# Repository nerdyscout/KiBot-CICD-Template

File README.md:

---

# KiCAD-CICD-Template

This repository provides different CI/CD workflows used for projects using [KiCAD](https://www.kicad.org/) and [PlatformIO](https://platformio.org).

## workflows

### KiBot

[KiBot](https://github.com/INTI-CMNB/KiBot/) is used to generate all kind of documentation from a KiCAD6 project.

Whenever a file matching `pcb/*.kicad_*` changes this workflow will trigger.

The following documents are generated on every build:

```
- pcb/cad/
   - dxf/
      - AutoCAD - DXF
   - boardview - BRD
   - 3D render - STEP
- pcb/docs/
   - bom/
      - Interactive BOM - HTML
      - Octopart list - CSV
      - KiCost - XLSX (disabled)
   - schematic - PDF
- pcb/img/
   - pcb/$fab/$style/
      - PCB top - SVG
      - PCB bottom - SVG
   - render/ (disabled)
      - PCB render - PNG
   - schematic - SVG
- pcb/gerbers - ZIP
```

### PlatformIO

used to rebuild your source code whenever it changes.

### REUSE

used to insure every file got a propper license. 

## getting started

- [ ] hit the "use this template" button and give your project a name
- [ ] clone this new repository localy
- [ ] replace content of README.md
- [ ] Code
   - [ ] put your code in the `src/` folder using platformio
- [ ] PCB
   - [ ] change the filenames in `pcb/*.kicad_*` matching your repository name
   - [ ] create your PCB
- [ ] run `reuse --lint`
   - [ ] make sure the licenses of `pcb/*` fits your needs
   - [ ] make sure the licenses of `src/*`, `include/*`, `lib/*`, `test/*` fits your needs
- [ ] commit and push all those changes regulary to your project

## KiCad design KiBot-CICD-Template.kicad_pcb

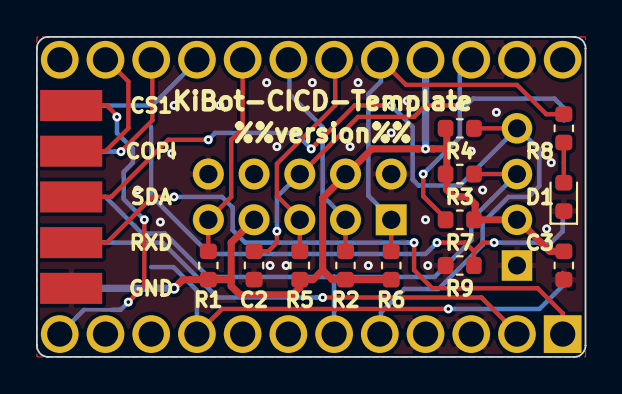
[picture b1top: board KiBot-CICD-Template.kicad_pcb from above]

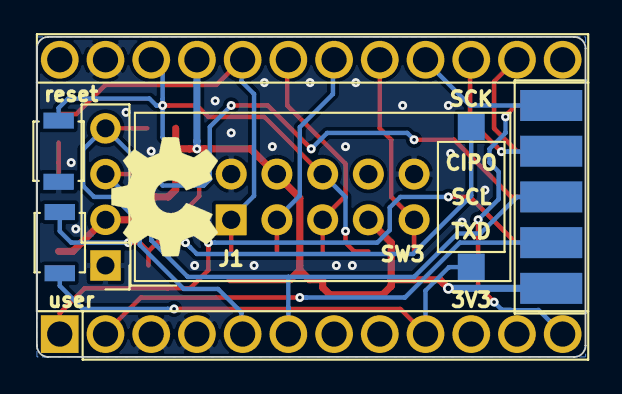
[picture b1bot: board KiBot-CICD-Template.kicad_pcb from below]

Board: 4 copper layers, 30.5 x 17.8 mm, 20 parts (8 on the bottom side), 18 nets.

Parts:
A1: Sparkfun_Pro_Micro
C2: 1µ; C_0603_1608Metric
C3: 100n; C_0603_1608Metric
D1: LED; LED_0603_1608Metric
J1: AVR-JTAG-10; IDC-Header_2x05_P2.54mm_Vertical
J2: UEXT_Host; UEXT
J3: Display; PinHeader_1x04_P2.54mm_Vertical
LOGO1: Logo_Open_Hardware_Small; OSHW-Symbol_6.7x6mm_SilkScreen
R1, R2, R3, R4, R5, R6, R7, R9: 4k7; R_0603_1608Metric
R8: 1k; R_0603_1608Metric
SW1: reset; SW_SPST_B3U-1000P
SW2: user; SW_SPST_B3U-1000P
SW3: user; SW_SPST_CK_RS282G05A3

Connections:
+3V3: A1.21, C3.1, J1.4, J1.7, J2.1, J3.2, R1.2, R2.2, R3.2, R4.2, R5.2, R6.2, R7.2
BTN: A1.9, SW2.2, SW3.2
CIPO: A1.15, J2.7
COPI: A1.14, J2.8
CS1: A1.12, J2.10
GND: A1.3, A1.4, A1.23, C2.2, C3.2, D1.1, J1.2, J1.10, J2.2, J3.1, R9.1, SW1.1
unnamed: D1.2, R8.1
unnamed: R9.2, SW2.1, SW3.1
RXD: A1.1, J2.4
SCK: A1.16, J2.9
SCL: A1.6, J2.5, J3.3, R3.1
SDA: A1.5, J2.6, J3.4, R4.1
TCK: A1.20, J1.1, R6.1, R8.2
TDI: A1.17, J1.9, R1.1
TDO: A1.18, J1.3, R2.1
TMS: A1.19, J1.5, R5.1
TXD: A1.2, J2.3
~RST: A1.22, C2.1, J1.6, R7.1, SW1.2

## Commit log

2021-11-30 testing complete overhaul of CICD template
2022-04-17 rework kibot to inherite from single file
2023-02-27 fixed URL for platformio.org
    www.platformio.org goes to a Graylog page.
2023-02-27 fixed URL for platformio.org (#6)
    www.platformio.org goes to a Graylog page.
2023-04-16 fix(pcbdraw): https://github.com/INTI-CMNB/KiBot/issues/424#issuecomment-1510326910
